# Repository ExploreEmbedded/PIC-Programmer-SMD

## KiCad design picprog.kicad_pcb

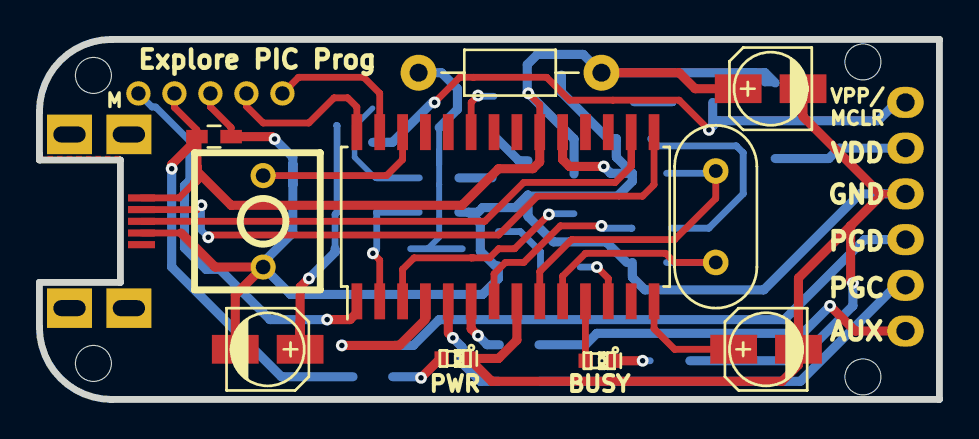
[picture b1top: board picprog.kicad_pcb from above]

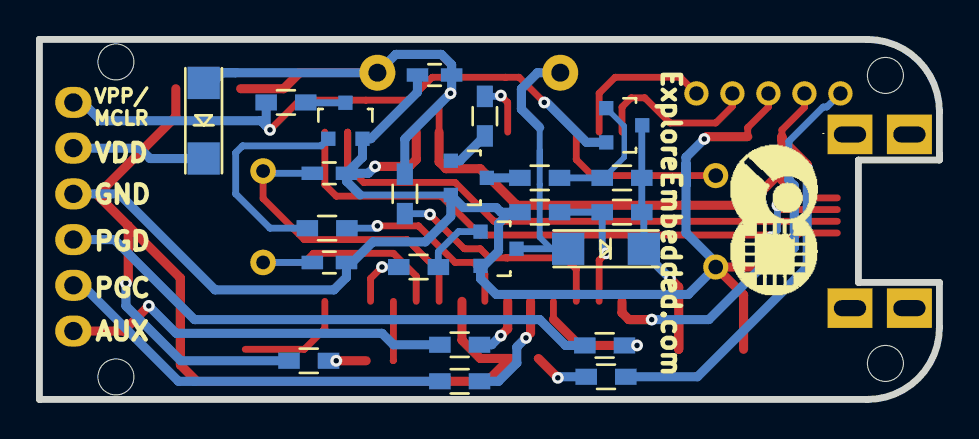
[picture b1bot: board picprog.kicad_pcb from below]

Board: 2 copper layers, 50.0 x 20.0 mm, 41 parts (24 on the bottom side), 35 nets.

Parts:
20Mhz1: CRYSTAL; HC-49V
C1, C3: 0.1uF; C_0603_HandSoldering
C2: 10uF, 50V; c_elec_4x5.8
C4, C7: 47uF,25V; c_elec_4x5.8
C5: 22pf; C_0603_HandSoldering
C6: 22pF; C_0603_HandSoldering
D1: LED-Red; LED-0603_NEW
D2: 1n4148; ZenerDiode_SMD_Small
D3: LED-Green; LED-0603_NEW
D4: 1N4148; ZenerDiode_SMD_Small
J1: USB_2; USB_Micro-B_SMD_NEW
L1: 680uH; Resistor_Horizontal_RM10mm
P1: CONN_01X01; LOGO (2)
P2: CONN_6; Pin_Header_Straight_1x06
P3, P4, P5, P6: CONN_01X01; 1pin
P7: CONN_01X05; Pin_Header_Straight_1x05_Pitch2.00mm
Q1: BC857; SOT-23
Q2, Q3, Q4: BC849; SOT-23
R1, R5: 220; R_0603_HandSoldering
R2, R3, R4: 33; R_0603_HandSoldering
R6: 100k; R_0603_HandSoldering
R7, R14: 4.7k; R_0603_HandSoldering
R8, R11, R13: 10k; R_0603_HandSoldering
R9: 100; R_0603_HandSoldering
R10: 1K; R_0603_HandSoldering
R12: 2.2k; R_0603_HandSoldering
SW1: SPST; SW_PUSH_SMALL_2pin_3D_xl
U1: PIC18F2550; SOIC-28_7.5x17.9mm_Pitch1.27mm

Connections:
/+5V: C1.1, C2.1, C3.1, D2.1, J1.1, L1.1, P7.2, R1.1, R14.1, U1.20
/BUSY: D1.1, U1.11
/D+: J1.3, U1.16
/D-: J1.2, U1.15
/ICSP_AUX: P2.6, R2.2
/ICSP_MCLR: R13.1, U1.7
/ICSP_PGC: P2.5, R3.2
/ICSP_PGD: P2.4, R4.2
/ICSP_VDD: D2.2, P2.2
/ICSP_VPP: P2.1, Q1.2, R9.1
/MCLR: P7.1, U1.1
/PGC: P7.5, U1.27
/PGD: P7.4, U1.28
/START_BT: SW1.2, U1.26
/VDD_FD: R14.2, U1.3
/VPP_FD: R7.2, R12.1, U1.2
/VPP_ON: R11.1, U1.23
/VPP_PUMP: R10.1, U1.12
GND: C1.2, C2.2, C3.2, C4.2, C5.2, C6.2, C7.2, D3.2, J1.4, P2.3, P7.3, Q2.2, Q3.2, Q4.2, R5.2, R12.2, SW1.1, U1.8, U1.19
unnamed: 20Mhz1.1, C6.1, U1.10
unnamed: 20Mhz1.2, C5.1, U1.9
unnamed: C4.1, U1.14
unnamed: C7.1, D4.2, Q1.3, R6.1, R7.1
unnamed: D1.2, R5.1
unnamed: D3.1, R1.2
unnamed: D4.1, L1.2, Q2.3
unnamed: Q1.1, R6.2, R8.1
unnamed: Q2.1, R10.2
unnamed: Q3.1, R11.2
unnamed: Q3.3, R8.2
unnamed: Q4.1, R13.2
unnamed: Q4.3, R9.2
unnamed: R2.1, U1.6
unnamed: R3.1, U1.5
unnamed: R4.1, U1.4

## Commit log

2016-05-18 Added Files
